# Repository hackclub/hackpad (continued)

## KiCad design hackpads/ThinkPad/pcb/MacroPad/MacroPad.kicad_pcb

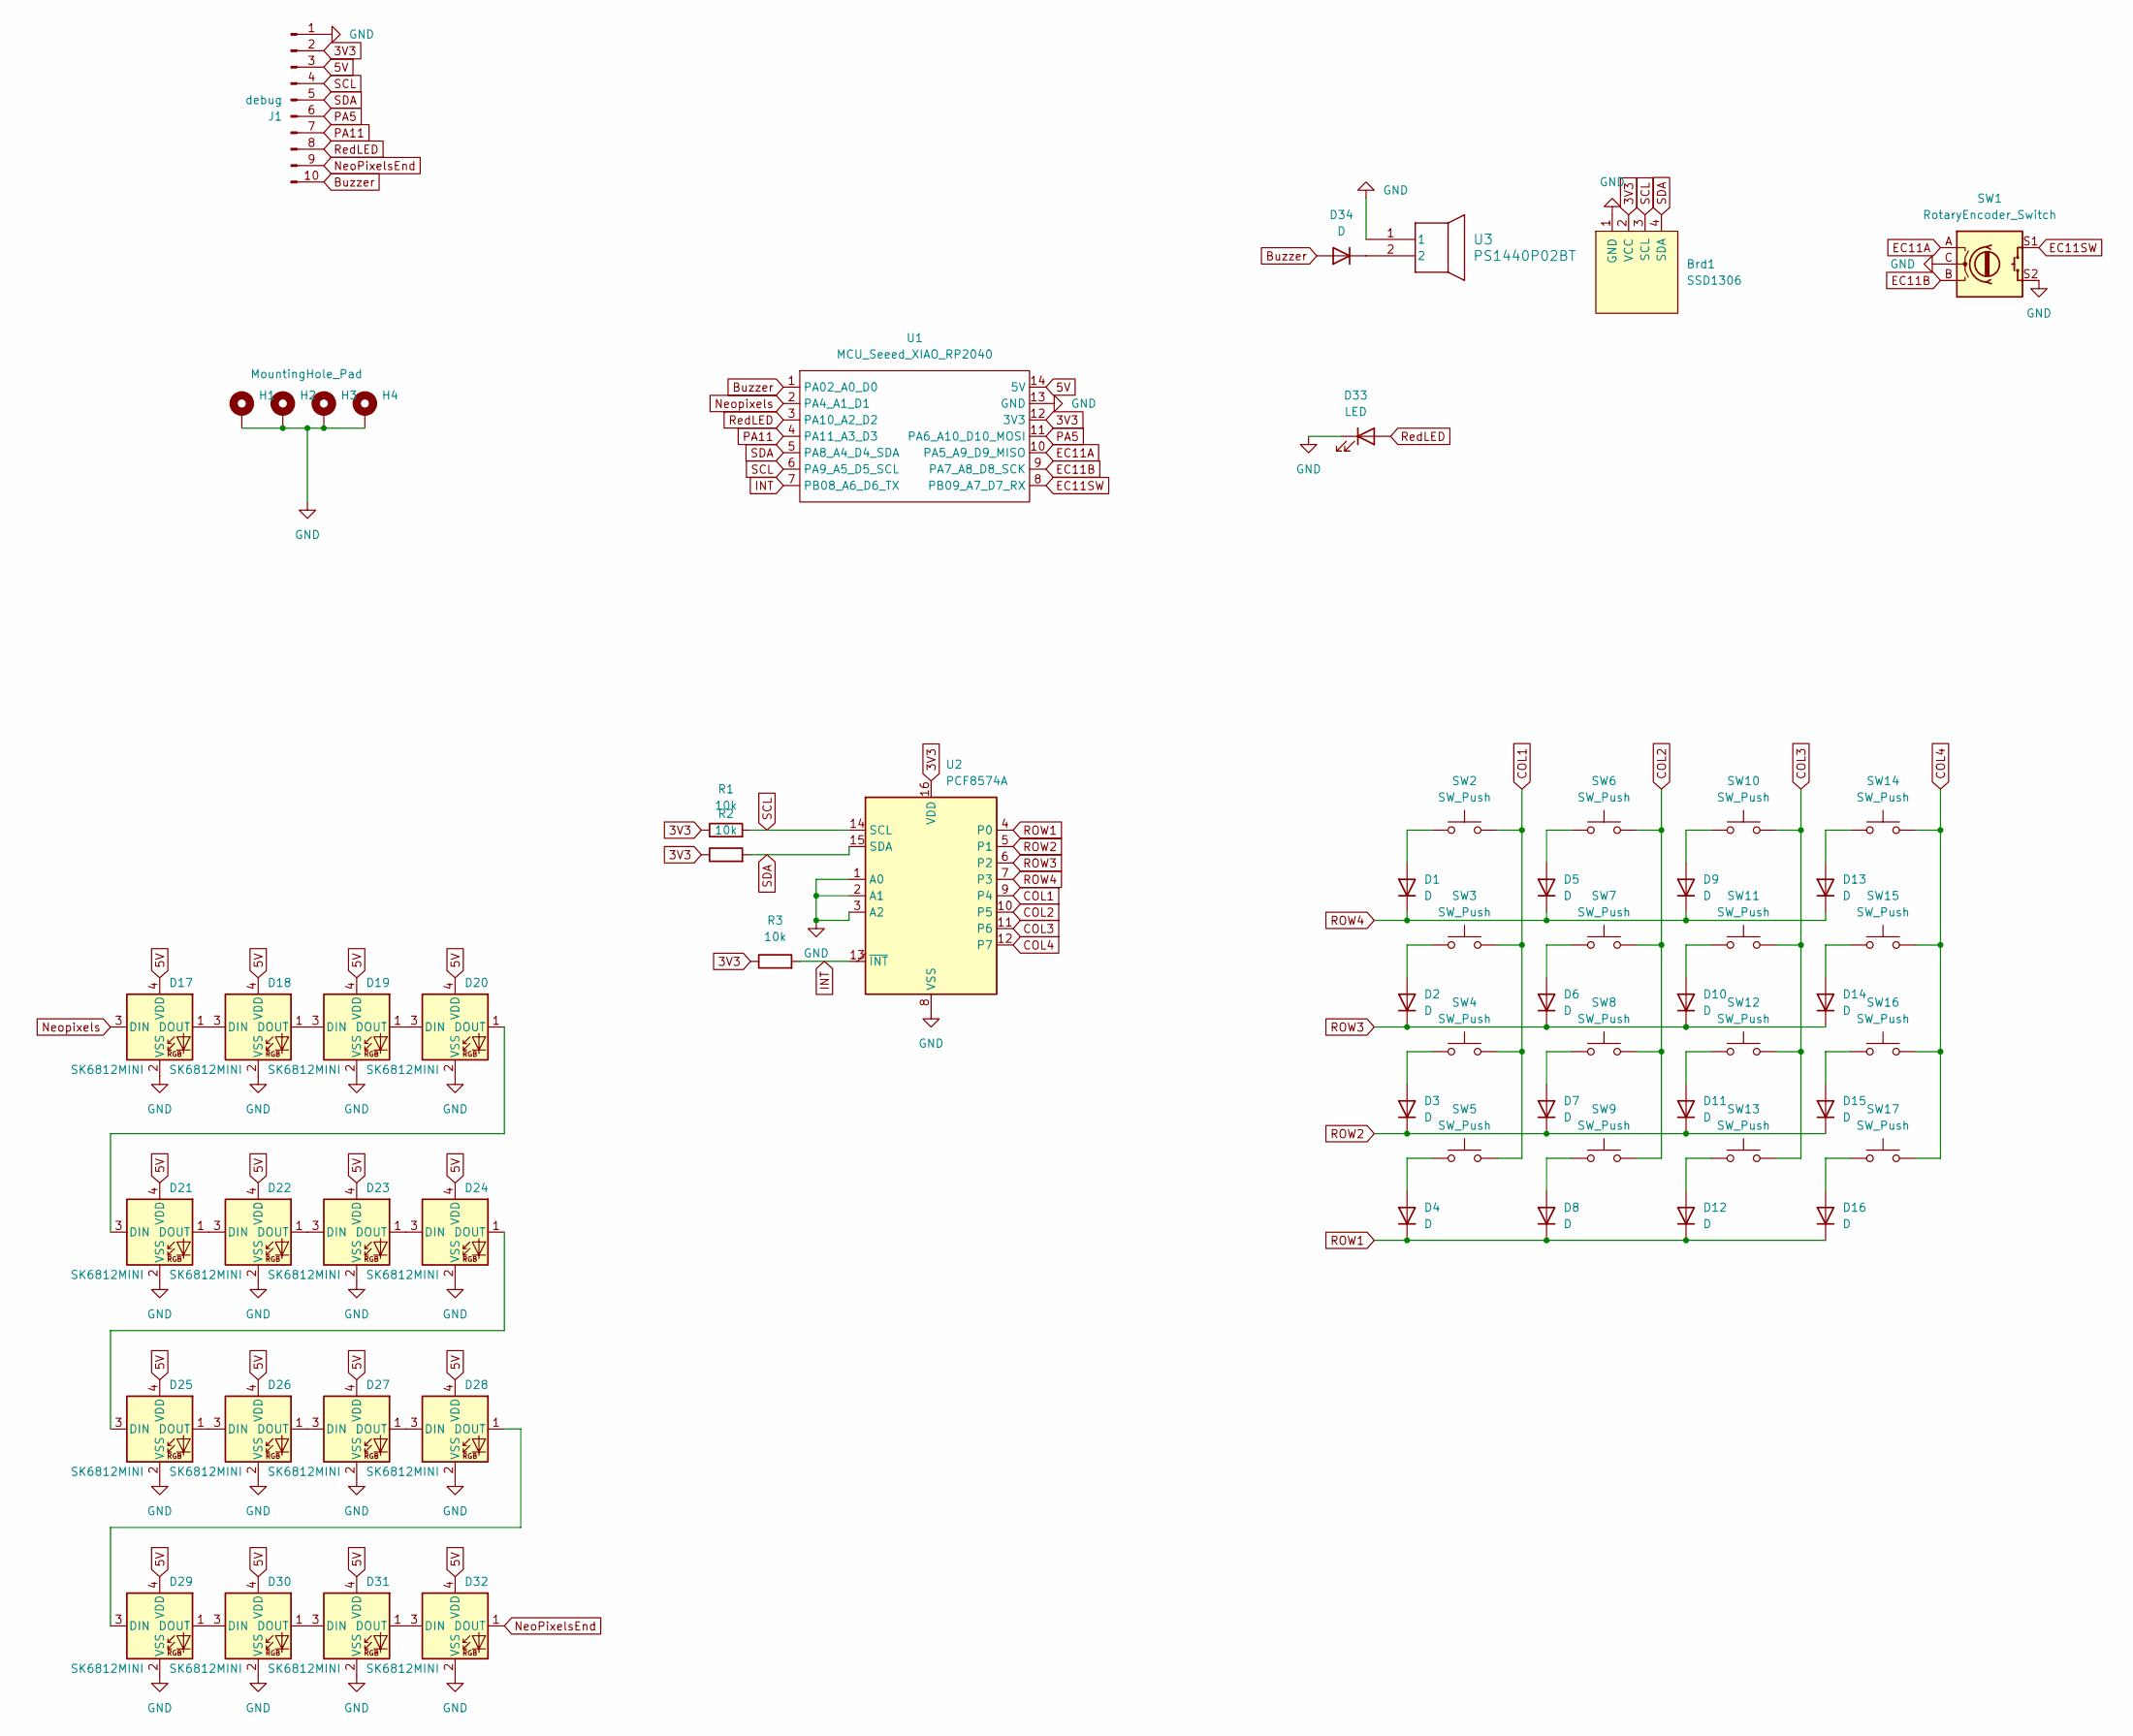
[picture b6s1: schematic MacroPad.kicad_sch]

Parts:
Brd1: SSD1306; 128x64OLED
D1, D2, D3, D4, D5, D6, D7, D8, D9, D10, D11, D12, D13, D14, D15, D16, D34: D; D_DO-35_SOD27_P7.62mm_Horizontal
D17, D18, D19, D20, D21, D22, D23, D24, D25, D26, D27, D28, D29, D30, D31, D32: SK6812MINI; MX_SK6812MINI-E
D33: LED; LED_D1.8mm_W3.3mm_H2.4mm
H1, H2, H3, H4: MountingHole_Pad; MountingHole_3.2mm_M3_Pad
J1: debug; PinHeader_1x10_P2.54mm_Vertical
R1, R2, R3: 10k; R_Axial_DIN0204_L3.6mm_D1.6mm_P7.62mm_Horizontal
SW1: RotaryEncoder_Switch; RotaryEncoder_Alps_EC11E-Switch_Vertical_H20mm
SW2, SW3, SW4, SW5, SW6, SW7, SW8, SW9, SW10, SW11, SW12, SW13, SW14, SW15, SW16, SW17: SW_Push; MX_Solder_1.00u
U1: MCU_Seeed_XIAO_RP2040; Seeed_XIAO_RP2040
U2: PCF8574A; N16_TEX
U3: PS1440P02BT; PS1440P02BT_TDK

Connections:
3V3: Brd1.2 (VCC), J1.2, R1.1, R2.1, R3.1, U1.12 (3V3), U2.16 (VDD)
5V: D17.4 (VDD), D18.4 (VDD), D19.4 (VDD), D20.4 (VDD), D21.4 (VDD), D22.4 (VDD), D23.4 (VDD), D24.4 (VDD), D25.4 (VDD), D26.4 (VDD), D27.4 (VDD), D28.4 (VDD), D29.4 (VDD), D30.4 (VDD), D31.4 (VDD), D32.4 (VDD), J1.3, U1.14 (5V)
Buzzer: D34.2 (A), J1.10, U1.1 (PA02_A0_D0)
COL1: SW2.2, SW3.2, SW4.2, SW5.2, U2.9 (P4)
COL2: SW6.2, SW7.2, SW8.2, SW9.2, U2.10 (P5)
COL3: SW10.2, SW11.2, SW12.2, SW13.2, U2.11 (P6)
COL4: SW14.2, SW15.2, SW16.2, SW17.2, U2.12 (P7)
EC11A: SW1.A, U1.10 (PA5_A9_D9_MISO)
EC11B: SW1.B, U1.9 (PA7_A8_D8_SCK)
EC11SW: SW1.S1, U1.8 (PB09_A7_D7_RX)
GND: Brd1.1 (GND), D17.2 (VSS), D18.2 (VSS), D19.2 (VSS), D20.2 (VSS), D21.2 (VSS), D22.2 (VSS), D23.2 (VSS), D24.2 (VSS), D25.2 (VSS), D26.2 (VSS), D27.2 (VSS), D28.2 (VSS), D29.2 (VSS), D30.2 (VSS), D31.2 (VSS), D32.2 (VSS), D33.1 (K), H1.1, H2.1, H3.1, H4.1, J1.1, SW1.C, SW1.S2, U1.13 (GND), U2.1 (A0), U2.2 (A1), U2.3 (A2), U2.8 (VSS), U3.1
INT: R3.2, U1.7 (PB08_A6_D6_TX), U2.13 (~INT)
NeoPixelsEnd: D32.1 (DOUT), J1.9
Neopixels: D17.3 (DIN), U1.2 (PA4_A1_D1)
unnamed: D1.2 (A), SW2.1
unnamed: D2.2 (A), SW3.1
unnamed: D3.2 (A), SW4.1
unnamed: D4.2 (A), SW5.1
unnamed: D5.2 (A), SW6.1
unnamed: D6.2 (A), SW7.1
unnamed: D7.2 (A), SW8.1
unnamed: D8.2 (A), SW9.1
unnamed: D9.2 (A), SW10.1
unnamed: D10.2 (A), SW11.1
unnamed: D11.2 (A), SW12.1
unnamed: D12.2 (A), SW13.1
unnamed: D13.2 (A), SW14.1
unnamed: D14.2 (A), SW15.1
unnamed: D15.2 (A), SW16.1
unnamed: D16.2 (A), SW17.1
unnamed: D17.1 (DOUT), D18.3 (DIN)
unnamed: D18.1 (DOUT), D19.3 (DIN)
unnamed: D19.1 (DOUT), D20.3 (DIN)
unnamed: D20.1 (DOUT), D21.3 (DIN)
unnamed: D21.1 (DOUT), D22.3 (DIN)
unnamed: D22.1 (DOUT), D23.3 (DIN)
unnamed: D23.1 (DOUT), D24.3 (DIN)
unnamed: D24.1 (DOUT), D25.3 (DIN)
unnamed: D25.1 (DOUT), D26.3 (DIN)
unnamed: D26.1 (DOUT), D27.3 (DIN)
unnamed: D27.1 (DOUT), D28.3 (DIN)
unnamed: D28.1 (DOUT), D29.3 (DIN)
unnamed: D29.1 (DOUT), D30.3 (DIN)
unnamed: D30.1 (DOUT), D31.3 (DIN)
unnamed: D31.1 (DOUT), D32.3 (DIN)
unnamed: D34.1 (K), U3.2
PA5: J1.6, U1.11 (PA6_A10_D10_MOSI)
PA11: J1.7, U1.4 (PA11_A3_D3)
ROW1: D4.1 (K), D8.1 (K), D12.1 (K), D16.1 (K), U2.4 (P0)
ROW2: D3.1 (K), D7.1 (K), D11.1 (K), D15.1 (K), U2.5 (P1)
ROW3: D2.1 (K), D6.1 (K), D10.1 (K), D14.1 (K), U2.6 (P2)
ROW4: D1.1 (K), D5.1 (K), D9.1 (K), D13.1 (K), U2.7 (P3)
RedLED: D33.2 (A), J1.8, U1.3 (PA10_A2_D2)
SCL: Brd1.3 (SCL), J1.4, R1.2, U1.6 (PA9_A5_D5_SCL), U2.14 (SCL)
SDA: Brd1.4 (SDA), J1.5, R2.2, U1.5 (PA8_A4_D4_SDA), U2.15 (SDA)

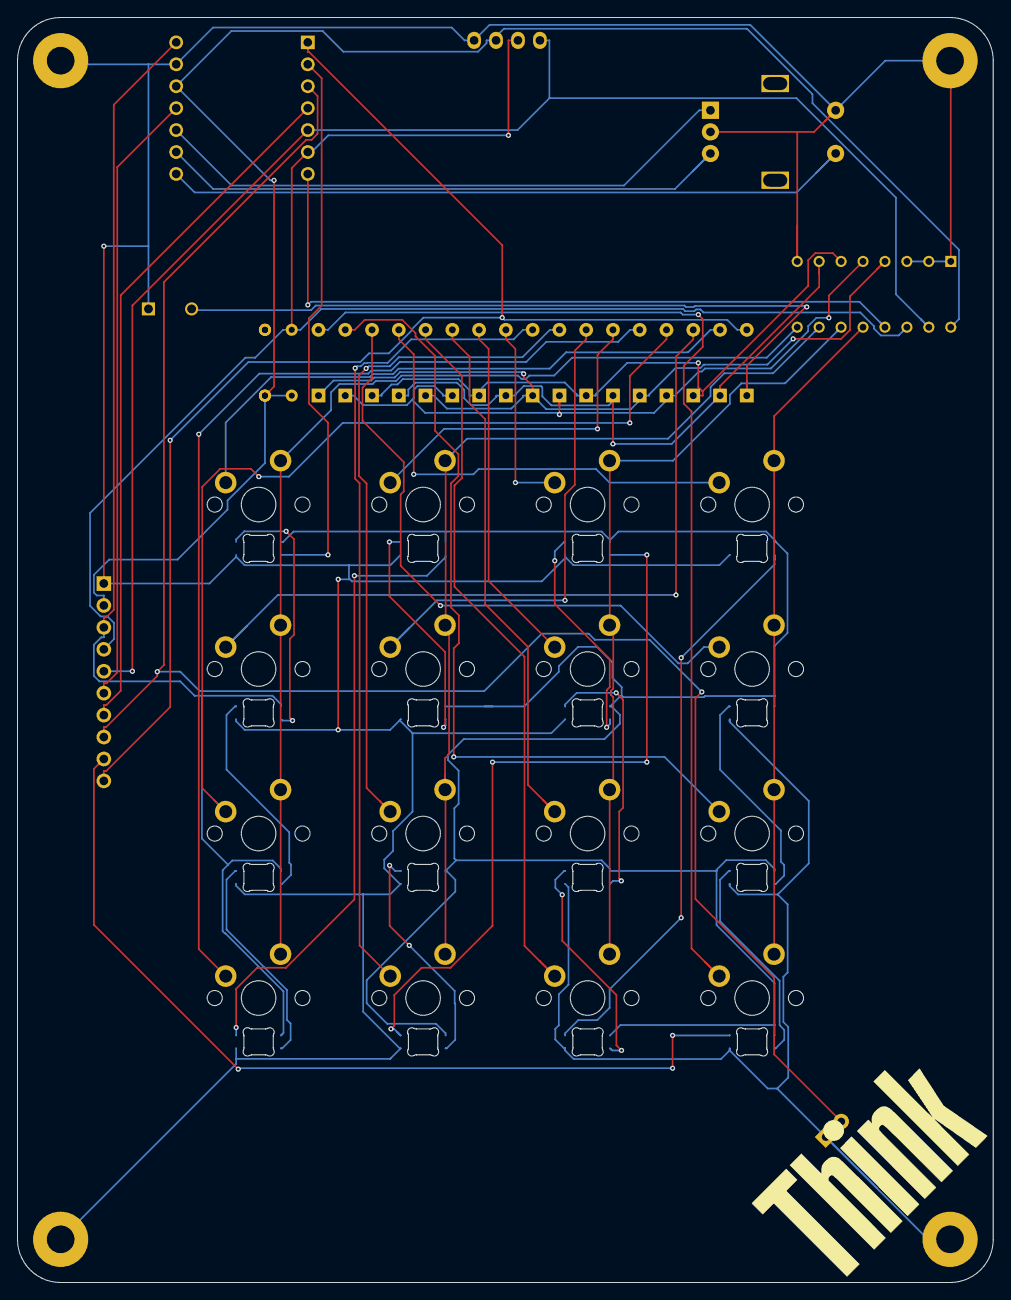
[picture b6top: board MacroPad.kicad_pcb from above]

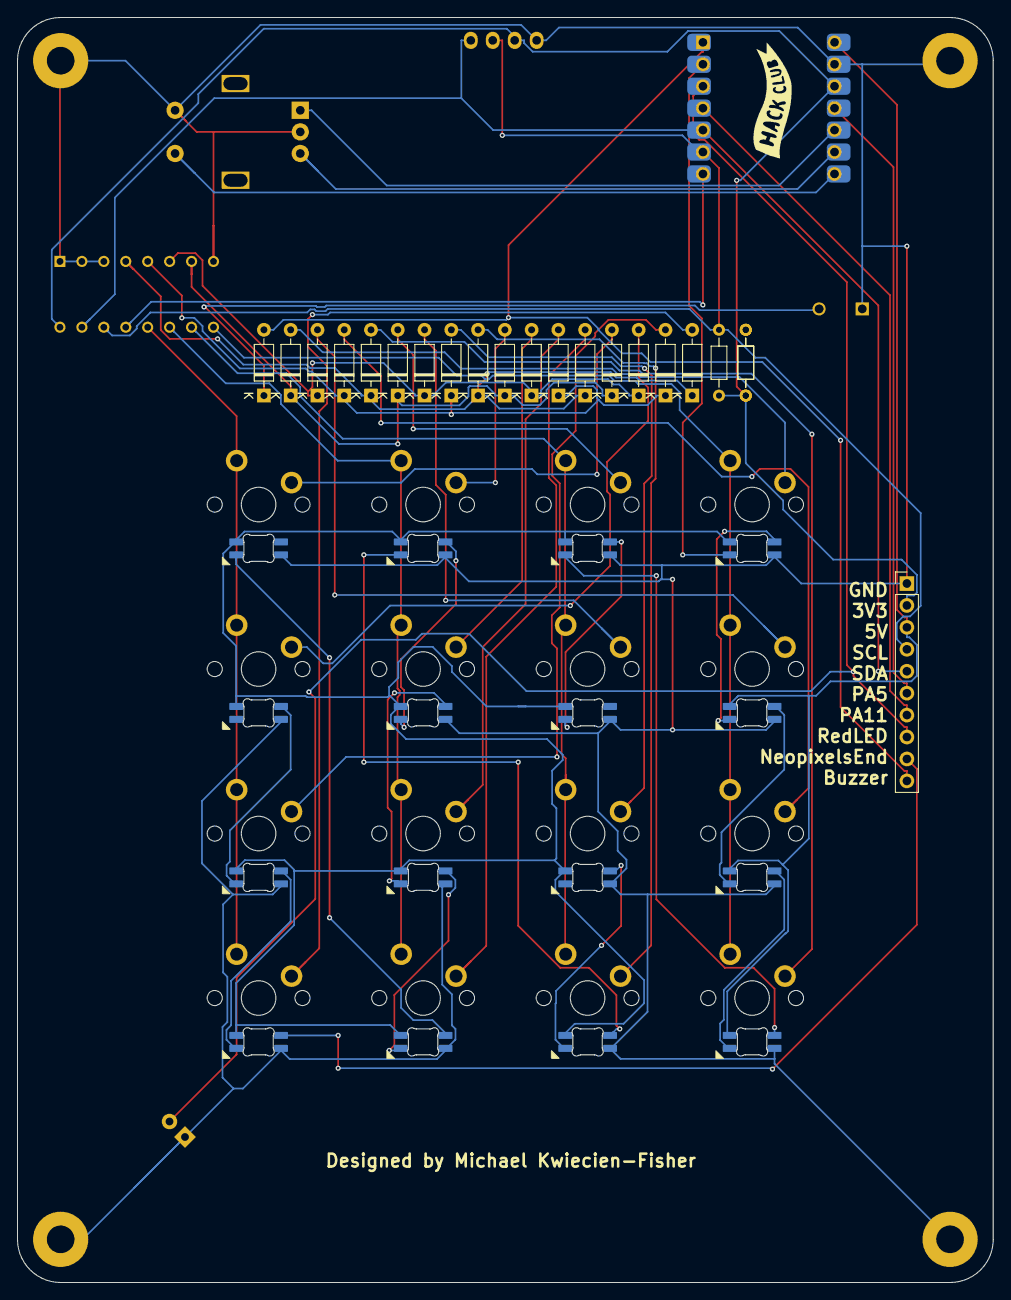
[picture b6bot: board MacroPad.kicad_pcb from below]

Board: 2 copper layers, 113.0 x 146.5 mm, 63 parts (22 on the bottom side), 55 nets.

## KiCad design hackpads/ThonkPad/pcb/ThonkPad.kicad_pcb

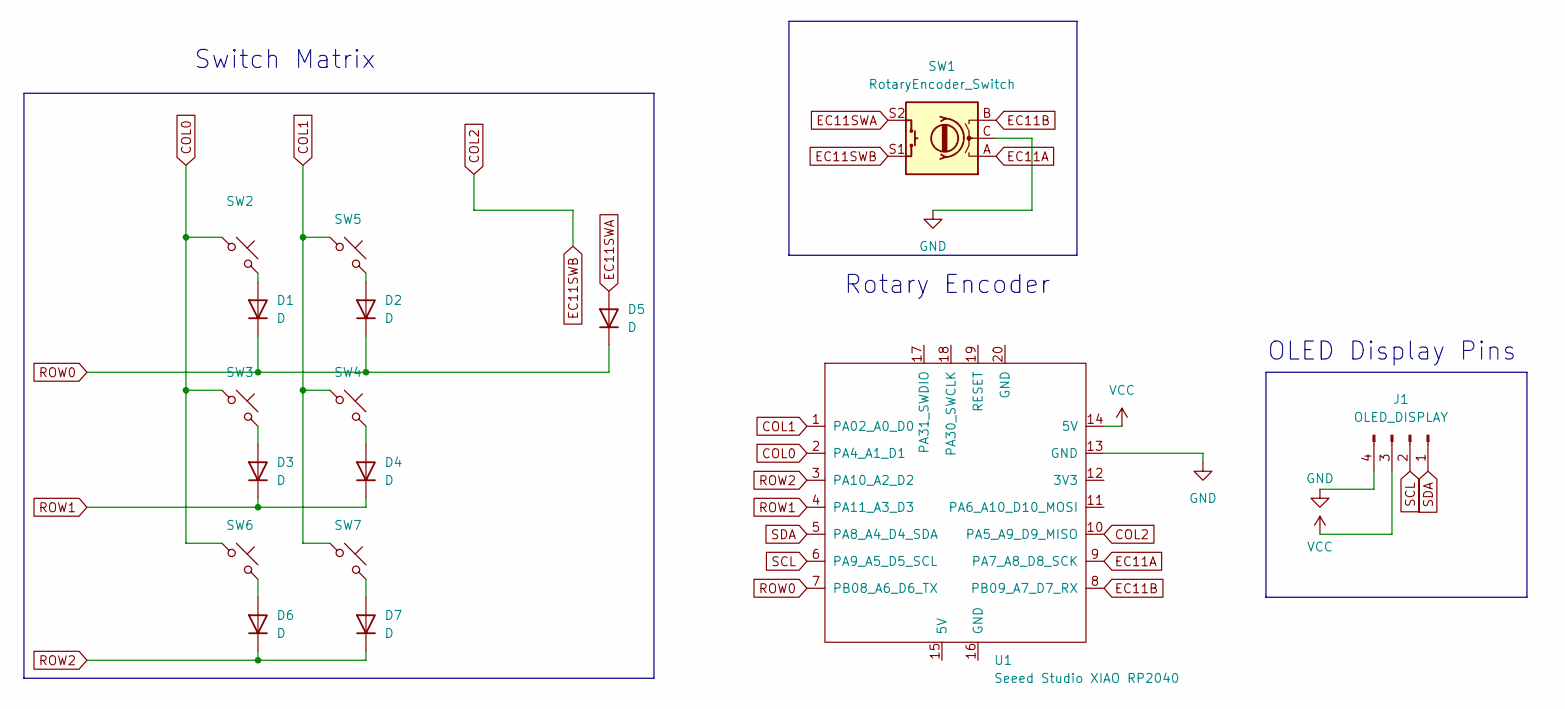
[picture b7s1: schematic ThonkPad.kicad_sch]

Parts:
D1, D2, D3, D4, D5, D6, D7: D; D_DO-35_SOD27_P7.62mm_Horizontal
J1: OLED_DISPLAY; PinHeader_1x04_P2.54mm_Vertical
SW1: RotaryEncoder_Switch; RotaryEncoder_Alps_EC11E-Switch_Vertical_H20mm
SW2, SW3, SW4, SW5, SW6, SW7: SW_Push_45deg; MX-Solderable-1U
U1: Seeed Studio XIAO RP2040; XIAO-Generic-Hybrid-14P-2.54-21X17.8MM

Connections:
COL0: SW2.1, SW3.1, SW6.1, U1.2 (PA4_A1_D1)
COL1: SW4.1, SW5.1, SW7.1, U1.1 (PA02_A0_D0)
COL2: SW1.S1, U1.10 (PA5_A9_D9_MISO)
EC11A: SW1.A, U1.9 (PA7_A8_D8_SCK)
EC11B: SW1.B, U1.8 (PB09_A7_D7_RX)
EC11SWA: D5.2 (A), SW1.S2
GND: J1.4, SW1.C, U1.13 (GND)
unnamed: D1.2 (A), SW2.2
unnamed: D2.2 (A), SW5.2
unnamed: D3.2 (A), SW3.2
unnamed: D4.2 (A), SW4.2
unnamed: D6.2 (A), SW6.2
unnamed: D7.2 (A), SW7.2
ROW0: D1.1 (K), D2.1 (K), D5.1 (K), U1.7 (PB08_A6_D6_TX)
ROW1: D3.1 (K), D4.1 (K), U1.4 (PA11_A3_D3)
ROW2: D6.1 (K), D7.1 (K), U1.3 (PA10_A2_D2)
SCL: J1.2, U1.6 (PA9_A5_D5_SCL)
SDA: J1.1, U1.5 (PA8_A4_D4_SDA)
VCC: J1.3, U1.14 (5V)

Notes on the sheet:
Switch Matrix
Rotary Encoder
OLED Display Pins

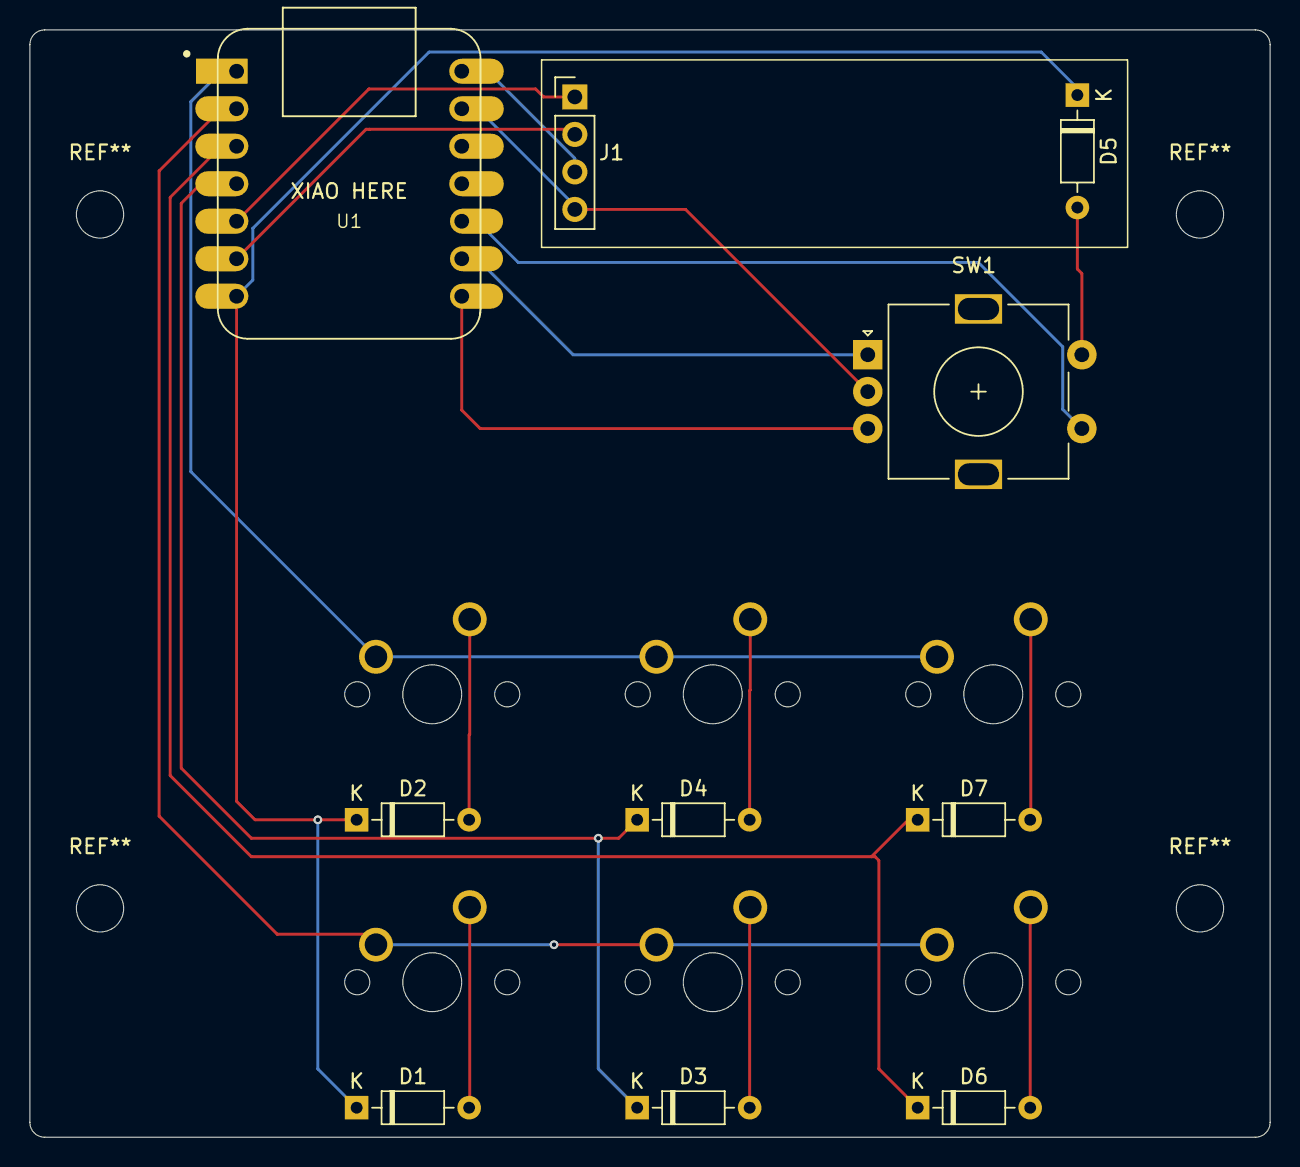
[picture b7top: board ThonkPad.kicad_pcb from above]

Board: 2 copper layers, 84.0 x 75.0 mm, 16 parts (0 on the bottom side), 19 nets.
